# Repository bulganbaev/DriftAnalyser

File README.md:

# ZVER L8

LED-контроллер линейки ZVER, бывший DriftAnalyser (ZverCustomLed).
Репозиторий: `~/Documents/Code/ZVER/L8`; старый путь `~/Documents/Code/DriftAnalyser` удалён. GitHub: [ZverCustom/l8](https://github.com/ZverCustom/l8/tree/pcb-v3), рабочая ветка — `pcb-v3`.
Актуальная восьмиканальная плата — [PCB v3](PCB/v3/README.md). Описание прошивки и шестиканальной v2 ниже относится к предыдущей ревизии.
Общая линейка и vault: `~/Documents/Code/ZVER`, `~/Documents/Code/bobr-projects/ZVER`.

Прошивка для платы на ESP32-S3, которая управляет шестью адресными 12 В лентами (WS2815) по данным с машины. Данные берутся с CAN-шины (OBD2 или пассивно с BMW MS43), с MS43 по K-line (DS2) и со встроенного гироскопа/акселерометра LSM6DS3TR-C. Настройка через веб-интерфейс GyverHub, который отдаётся с самой платы по Wi-Fi, приложение не нужно.

## Железо

Прошивка для **платы v2** (KiCad, `PCB/v2/`, подробно в её README). Прошивка под первую
ревизию (EasyEDA, `PCB/`, MPU-6050, 5 В ленты) осталась на `main` до слияния `fw-v2`.

| Узел | Что стоит |
|---|---|
| Контроллер | ESP32-S3-WROOM-1 N16R2, USB-C на native USB |
| Ленты | 6 × JST VH, только 12 В (WS2815), данные через 74HCT245 |
| Питание лент | ключ BTS7002-1EPP, включается из прошивки, ток читается через IS |
| CAN | TJA1051, пин S (silent) управляется из прошивки |
| K-line | TJA1027, UART1, перемычка JP2 = подтяжка 510 Ом на VBAT |
| IMU | LSM6DS3TR-C, I2C 0x6A |
| SD | microSD, в прошивке пока не задействована |

### Пины (`src/pins/pins.h`)

| Сигнал | GPIO |
|---|---|
| LED 1..6 | 4, 5, 6, 7, 15, 16 |
| LED_PWR_EN (ключ лент) | 10 |
| LED_ISENSE (ADC) | 2 |
| VBAT_SENSE (ADC) | 1 |
| STATUS_LED | 11 |
| I2C SDA / SCL | 8 / 9 |
| IMU INT1 | 17 (не используется) |
| K-line RX / TX | 12 / 13 |
| CAN RX / TX / STB | 21 / 18 / 14 |
| BOOT | 0 |

### Питание лент и защита

Ключ лент выключен до первого кадра (чёрного), потом включён, пока включён Master.
Ток пересчитывается из IS: `I = V_IS × 22700 / 470`. Прошивка выключает ключ и держит
выключенным (латч), если сглаженный ток выше «LED max current» (по умолчанию 15 А)
дольше 100 мс, или если IS выше 1.6 В дольше 50 мс (сигнал fault самого BTS7002).
Сброс кнопкой «Reset power latch» на странице System. VBAT = `V × 5.7` (делитель 47k/10k).

Светодиод статуса: горит во время загрузки, мигает 1 Гц в работе, 5 Гц при сработавшем латче.

### Перемычки

- JP1 — терминатор 120 Ом на CAN. На шине машины не ставить.
- JP2 — подтяжка K-line к VBAT. Нужна, если DME сама шину не тянет; без 12 В трансивер K-line не работает вообще.

## Сборка и прошивка

PlatformIO, окружение `esp32s3box`.

```
~/.platformio/penv/bin/pio run -e esp32s3box            # сборка
~/.platformio/penv/bin/pio run -e esp32s3box -t upload  # заливка
~/.platformio/penv/bin/pio device monitor -b 115200     # монитор
```

Если `pio` есть в PATH, полный путь не нужен. В VS Code то же самое кнопками PlatformIO в статус-баре.

Плата видна как `/dev/cu.usbmodemXXXX` (native USB CDC), лог на 115200. При открытии порта плата может сброситься по DTR/RTS, это нормально.

Важное в `platformio.ini`:

| Параметр | Зачем |
|---|---|
| `board_build.partitions = default_16MB.csv` | под прошивку 6.5 МБ вместо дефолтных 1.3 МБ |
| `-D GH_INCLUDE_PORTAL` | веб-интерфейс GyverHub зашит в прошивку и отдаётся с платы |
| `-D GH_NO_STREAM` | GyverHub не льёт свои пакеты в Serial |
| `-D FASTLED_ESP32_FLASH_LOCK=1` | запись во флеш ждёт окончания вывода на ленты, иначе паника `Cache disabled but cached memory region accessed` |

Библиотека GyverHub тянется с git HEAD (репозиторий заархивирован), магазинные приложения с ней несовместимы (`Device has newer API`). Поэтому интерфейс встроен в прошивку.

### Дефолтная Wi-Fi сеть

Скопировать `src/config/secrets.example.h` в `src/config/secrets.h` и вписать SSID и пароль. Файл в `.gitignore`. Эти значения используются как стартовые при чистом файле настроек, потом меняются из интерфейса.

## Wi-Fi

Плата объявляет себя по mDNS как `zvercustom`, в той же сети интерфейс открывается по `http://zvercustom.local`.

Прошивка по Wi-Fi без кабеля, из корня проекта после `pio run`:

```
curl -F "file=@.pio/build/esp32s3box/firmware.bin" "http://zvercustom.local/hub/ota?client_id=cli&type=flash"
```

Плата сама перезагрузится, в логе на странице System будет `reboot: OTA update`. То же самое доступно кнопкой в информации об устройстве в интерфейсе.

- При старте плата подключается к сохранённой сети (STA).
- Если за 20 с не подключилась, поднимает свою точку `ZverCustomLed` / `qwerty12345`, IP 192.168.4.1, и продолжает пробовать STA каждые 30 с.
- Как только STA подключилась, точка гасится. Если STA пропала на 20 с, точка поднимается снова.
- Пустой SSID = только своя точка.
- Веб-интерфейс: `http://<ip платы>`, на точке `http://192.168.4.1` (открывается как captive portal). Только http.
- OTA-прошивка и файловый менеджер доступны во вкладке информации об устройстве в интерфейсе GyverHub.

## Веб-интерфейс

Меню сверху, шесть страниц.

### Dashboard

Главный выключатель Master, статус Wi-Fi, gauge RPM / Speed / Temp / Throttle / Lateral G / Yaw, статус CAN, кнопка Reboot.

### LEDs

Настройки выбранной ленты (Strip 1..6):

| Настройка | Что делает |
|---|---|
| Strip N enabled | вкл/выкл вывод на ленту |
| Reverse | перевернуть направление |
| Mode | Animation / Scale / Hybrid |
| Scale source | RPM / Speed / Throttle / Lateral G / Yaw rate (для Scale и Hybrid) |
| Animation | одна из 16 анимаций (для Animation, а в Hybrid — то, что крутится ниже минимума) |
| Color | цвет для одноцветных анимаций |
| Strip brightness | яркость ленты 0–100 |
| LED count | число светодиодов, 1..1000, применяется на лету |
| Color order | RGB / GRB / BGR / RBG / GBR / BRG, тоже на лету |
| Grow from middle + Middle LED | шкала растёт от указанного светодиода в обе стороны; для G и Yaw знак значения выбирает сторону |
| Apply to all strips | скопировать настройки этой ленты на остальные (кроме числа светодиодов) |

Режимы: Animation — просто анимация. Scale — шкала по выбранному источнику, семь цветовых зон от синего к пурпурному. Hybrid — шкала, когда источник выше минимума, иначе анимация.

Анимации: Static Color, Theater Chase, Color Wave, Breathing Light, Rainbow Cycle, Snake, Meteor Rain, Twinkle, Running Lights, Larson Scanner, Fire, Police, Confetti, Color Wipe, Sinelon, G Force. У каждой ленты своё состояние, две ленты на одной анимации друг другу не мешают.

Глобальные:

| Настройка | Что делает |
|---|---|
| Animation speed | частота кадров для всех анимаций (у Police и Sinelon ещё и период) |
| Global brightness | общая яркость 0–100 |
| Scale min / max RPM | диапазон шкалы по оборотам |
| Shift light RPM / Shift color | выше этого порога вся лента в режиме шкалы по RPM мигает выбранным цветом; 0 = порог равен max RPM |
| Full scale km/h / G / yaw | полная шкала для источников Speed, Lateral G, Yaw |
| Engine off / no data | что делать, когда мотор заглушен или данных нет: Keep running / Dim (до Dim to %) / Off |
| Power limit mA at 12V | программный лимит тока FastLED (оценка по яркости), 0 = выключен. Аппаратная защита — LED max current на странице System |
| Presets | три слота, Save / Load всего набора настроек лент и глобальных |

«Мотор заглушен» = нет свежих данных с CAN или обороты ниже 300.

### CAN

Выбор источника OBD2 / BMW MS43 / Sniffer (переключается на лету, драйвер перезапускается), статус драйвера и потока, сырые значения RPM / Speed / Temp / Throttle. В режиме Sniffer — таблица кадров по ID, обновляется раз в секунду.

### Wi-Fi

SSID, пароль, кнопка Reconnect, статус, IP и RSSI в сети, состояние своей точки, MAC.

### IMU

Gauge Lateral G и Yaw, выбор осей (±X / ±Y / ±Z) для поперечного ускорения и для угловой скорости, кнопка Calibrate (машина ровно, мотор заглушен — текущее показание становится нулём, смещения сохраняются), сырые значения по трём осям и температура чипа.

### System

VBAT, ток лент, состояние ключа и причина латча, «LED max current», кнопка «Reset power latch». Ниже uptime, причина последнего сброса, свободная память, дата сборки, занятость файловой системы, хвост лога, кнопки Refresh log / Clear log / Reboot.

## CAN

Скорость 500 кбит/с во всех режимах.

**OBD2.** Активный опрос mode 01 на 0x7DF, ответ ждётся с 0x7E8..0x7EF. PID 0x0C (RPM), 0x0D (скорость), 0x11 (дроссель), 0x05 (температура ОЖ), по кругу, пауза 50 мс между запросами, таймаут ответа 200 мс. Неблокирующий.

**BMW MS43.** Плата в listen-only, ничего не передаёт и не подтверждает кадры. Декодирует:

| ID | Данные | Формула |
|---|---|---|
| 0x316 (DME1) | обороты | `((b3 << 8) \| b2) / 6.4` |
| 0x329 (DME2) | температура ОЖ, дроссель | `b1 * 0.75 - 48`, `b5 * 100 / 254` |
| 0x153 (ASC1) | скорость | `((b2 << 8) \| b1) / 128` — не проверено, калибровать по дампу |

У MS43 диагностика по K-line, OBD2-запросы он не понимает. CAN между DME, приборкой, ABS и АКПП выведен на разъём X60004: пин 36 = CAN H (жёлто-красный), пин 37 = CAN L (жёлто-коричневый). Масса платы на кузов, H1 снять.

**BMW MS43 K-line (DS2).** UART1 9600 8E1, по кругу запрос статуса `12 05 0B 03 1F`, ответ
45 байт. Эхо собственного запроса трансивер возвращает, оно сверяется и отбрасывается.
Таймаут 400 мс, пауза 10 мс. CAN в этом режиме остаётся listen-only и не декодируется.

| Байт ответа | Данные | Формула |
|---|---|---|
| 3–4 | обороты | u16 big-endian |
| 5 | скорость, км/ч | как есть |
| 6–7 | педаль, ° | u16 × 0.0018311 → % по полному ходу 80° (подобрать в машине) |
| 8–9 | дроссельная заслонка, ° | u16 × 0.0018311 |
| 12 / 13 | воздух на впуске / ОЖ, °C | × 0.75 − 48 |
| 43 | напряжение, В | × 0.10156 |

Смещения из таблицы SGBD MS430DS0 (`ms430ds0_ds2.b1v`) и сверены с реальным ответом
с форума (747 об/мин, ОЖ 67.5 °C, 13.7 В), но на нашей машине **ещё не проверены**.
На странице CAN в этом режиме: декодированные значения, последний сырой кадр и поле для
произвольного запроса в hex (адрес, длина, данные; xor дописывается сам).

**Sniffer.** Listen-only, все кадры в таблицу по ID (до 64 ID): длина, последние байты, кадров в секунду, всего. Та же таблица печатается в Serial не чаще двух раз в секунду на ID.

Если данных нет 3 с, обороты, скорость и дроссель сбрасываются в 0, температура остаётся.

## Хранение настроек

Всё в LittleFS, файл `/settings.dat` через FileData. Буква-ключ в `src/settings/settings.cpp` (сейчас `'C'`) работает как версия структуры: при изменении `SavedData` или буквы файл перезаписывается дефолтами. Запись отложенная, через `fileData.update()` после изменений в интерфейсе.

Лог `/log.txt`: старт с причиной сброса и датой сборки, Wi-Fi подключился/пропал, точка поднялась, смена режима CAN, найден/потерян IMU, перезагрузки из интерфейса и по OTA. При 24 кБ переезжает в `/log.old`. Файлы можно скачать через файловый менеджер GyverHub.

## Структура исходников

| Модуль | Что делает |
|---|---|
| `src/main.cpp` | setup/loop, порядок инициализации |
| `src/config/` | AP SSID/пароль, число лент, `secrets.h` с дефолтной сетью |
| `src/pins/` | все GPIO |
| `src/settings/` | структура настроек, загрузка/сохранение, пресеты |
| `src/net/` | Wi-Fi: STA с откатом на AP, строки статуса |
| `src/hub/` | страницы GyverHub |
| `src/led_control/` | ленты: анимации, шкала, шифт-лайт, выходной буфер с реверсом/яркостью/порядком цветов, лимит тока |
| `src/can_bus/` | обёртка над TWAI, normal / listen-only, перезапуск |
| `src/obd2/` | неблокирующий опрос PID |
| `src/vehicle/` | общие данные машины, режимы CAN, декодер MS43, сниффер |
| `src/imu/` | LSM6DS3TR-C по регистрам, фильтр, калибровка, поперечное G и yaw |
| `src/power/` | ключ лент, латч по току, VBAT, светодиод статуса |
| `src/kline/` | DS2 по K-line, опрос MS43 |
| `lib/ds2/`, `lib/power_latch/` | чистая логика без Arduino, тесты `pio test -e native` |
| `src/system/` | причина сброса, uptime, лог на LittleFS |

## Известные проблемы и что дальше

- Формула скорости для 0x153 взята с форума и не проверена, сверять по сниффер-дампу на ходу.
- MS43-декодер на живой машине ещё не гонялся, начинать со Sniffer и смотреть, что летит.
- Ориентация IMU зависит от того, как плата стоит в машине: выбрать оси на странице IMU и откалибровать на ровной площадке.
- DS2-смещения и полный ход педали не проверены на машине.
- SD-карта не задействована.
- Разъёмы лент и OBD на v2 стоят вертикально, корпус под вставленные фишки надо поднимать.

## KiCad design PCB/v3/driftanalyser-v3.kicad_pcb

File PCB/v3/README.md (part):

# ZVER L8 PCB v3

Product name: ZVER L8 (formerly DriftAnalyser). Existing technical filenames and fabrication outputs retain their names.

Car LED controller: eight switched 12 V WS2812 strip channels, CAN, K-line, IMU, three inputs,
ESP32-S3. 55 × 112 mm, 6 layers, every part on the top side.

Everything is generated from `gen/` (`gen/model.py` = parts and nets, `gen/placement.py`,
`gen/pcb_builder.py` = copper, `gen/route.py` = replays the committed Freerouting session
`fab/route.ses`, `gen/export.py` = fab files). `bash gen/build.sh` rebuilds schematic, board, routing,
fab files and runs the tests. Do not hand-edit the `.kicad_sch` / `.kicad_pcb` files. What goes to
the fab and how to order it: [`fab/README-fab.md`](fab/README-fab.md).

## What is on the board

| block | parts |
| --- | --- |
| +12 V in | **J2** M6 terminal (Würth WP-BUCF REDCUBE PRESS-FIT 7461059: 13 × 13 mm brass block, internal M6 thread, 16 press-fit pins; we press it in, red boot), D1 SMCJ24CA TVS, **U2 LM74700-Q1** ideal diode with **Q1/Q2 2 × BSC016N06NS** (60 V) VIN → VBUS |
| battery negative | **J5** M6 terminal (same part, pressed in by us, black boot) = GND. The strips' return (35..40 A) comes in here and goes through In1 (solid GND) and the GND fills to J1 row 4 |
| logic supply | **U7 LMR36520** buck (VIN 4.2..65 V, abs max 70 V; replaces v2's AP63200) → 5.4 V → D6 → 5V, U8 AP7361C → 3V3; USB-C J3 (U9 ESD) feeds 5V through D8 |
| wake / hold | IGN (J1.24) or HOLD (GPIO41) enables the buck through D4/D5; IGN off and HOLD low = buck off |
| strip outputs | **U10..U13 BTS7008-2EPA** (dual high-side, exposed pad = VBUS), 8 channels × 5 A; inputs, DEN, DSEL from **U14 PCA9555 @ 0x20**; one shared IS line (R49 1.2k) to GPIO2 |
| strip data | U15/U16 74HCT245 (3V3 → 5 V), 33 R series + PESD5V0S1BA per line |
| comms | U4 TJA1051T/3 CAN (JP2 120 R termination), U5 TJA1027 K-line (JP1 510 R pull-up to VBUS), D20 PESD1CAN |
| inputs | IN1..IN3: SMAJ24A, 10k / 33k / 10k divider to the ADC, switchable 10k pull (see firmware notes) |
| sensor 5 V | U6 TPS2553 (~130 mA limit, EN / FAULT on U14 / GPIO47), D7 reverse block, out on J1.23 |
| MCU | U1 ESP32-S3-WROOM-1U-N16R2 (u.FL), U3 LSM6DS3TR-C IMU (I2C 0x6A), SW1 BOOT, SW2 EN, J4 UART0 |

## J1 pinout (TE 6437288-1, Superseal 1.0, 34 pos)

Re-pinned during routing (task 11 ruling, spec §3 note): all eight LEDn +12 V in row 1, each right
above its own switch output; the eight strip grounds in row 4, each in the same column as its +12 V;
data, CAN, K-line, IGN, inputs and the sensor 5 V in rows 2–3. Pin numbers are TE's, as moulded on
the housing.

<!-- j1-table: generated by gen/export.py, do not edit -->

| row | pin | net | signal |
| --- | --- | --- | --- |
| 1 | 1 | `LED2_12V` | LED2 +12 V (U10 OUT1) |
| 1 | 2 | `LED1_12V` | LED1 +12 V (U10 OUT0) |
| 1 | 3 | `LED6_12V` | LED6 +12 V (U12 OUT1) |
| 1 | 4 | `LED5_12V` | LED5 +12 V (U12 OUT0) |
| 1 | 5 | `GND` | GND, signal return |
| 1 | 6 | `LED4_12V` | LED4 +12 V (U11 OUT1) |
| 1 | 7 | `LED3_12V` | LED3 +12 V (U11 OUT0) |
| 1 | 8 | `LED8_12V` | LED8 +12 V (U13 OUT1) |
| 1 | 9 | `LED7_12V` | LED7 +12 V (U13 OUT0) |
| 2 | 10 | `LED2_DO` | LED2 data |
| 2 | 11 | `LED1_DO` | LED1 data |
| 2 | 12 | `LED6_DO` | LED6 data |
| 2 | 13 | `LED5_DO` | LED5 data |
| 2 | 14 | `IN1` | input 1 |
| 2 | 15 | `LED4_DO` | LED4 data |
| 2 | 16 | `LED3_DO` | LED3 data |
| 2 | 17 | `LED8_DO` | LED8 data |
| 3 | 18 | `CANH` | CAN high |
| 3 | 19 | `CANL` | CAN low |
| 3 | 20 | `KLINE` | K-line |
| 3 | 21 | `IN2` | input 2 |
| 3 | 22 | `IN3` | input 3 |
| 3 | 23 | `5V_SENS` | 5 V sensor supply (U6, switched, ~130 mA limit) |
| 3 | 24 | `IGN` | ignition (wakes the board) |
| 3 | 25 | `LED7_DO` | LED7 data |
| 4 | 26 | `GND` | GND, LED2 strip return |
| 4 | 27 | `GND` | GND, LED1 strip return |
| 4 | 28 | `GND` | GND, LED6 strip return |
| 4 | 29 | `GND` | GND, LED5 strip return |
| 4 | 30 | `GND` | GND, signal return |
| 4 | 31 | `GND` | GND, LED4 strip return |
| 4 | 32 | `GND` | GND, LED3 strip return |
| 4 | 33 | `GND` | GND, LED8 strip return |
| 4 | 34 | `GND` | GND, LED7 strip return |

Top view, J1 at the top edge (mating face toward the edge, row 4 nearest it):

```
row 4: 34 LED7_GND     33 LED8_GND     32 LED3_GND     31 LED4_GND     30 SIG2_GND     29 LED5_GND     28 LED6_GND     27 LED1_GND     26 LED2_GND
row 3:         25 LED7_DO      24 IGN          23 5V_SENS      22 IN3          21 IN2          20 KLINE        19 CANL         18 CANH
row 2:         17 LED8_DO      16 LED3_DO      15 LED4_DO      14 IN1          13 LED5_DO      12 LED6_DO      11 LED1_DO      10 LED2_DO
row 1:  9 LED7_12V      8 LED8_12V      7 LED3_12V      6 LED4_12V      5 SIG1_GND      4 LED5_12V      3 LED6_12V      2 LED1_12V      1 LED2_12V
```

<!-- /j1-table -->

Harness: crimp by pin number, not by position or wire colour. Each strip is three wires on three
fixed pins: its +12 V in row 1, its ground in row 4 straight below that, its data in row 2 or 3 (see
the table). Keep each strip's +12 V and ground in the same cable. CANH/CANL (18/19) are a twisted
pair. Pins 5 and 30 are signal grounds for the sensor / input side. Every cavity is used, so no
sealing plugs are needed.

## Jumpers

| jumper | fitted | open |
| --- | --- | --- |
| JP1 (silk "JP1 K-LINE") | 510 R K-line pull-up to VBUS: car without its own pull-up / board is the master | CAN-only car, or the bus already has a pull-up |
| JP2 (silk "JP2 CAN TERM") | 120 R between CANH and CANL: board is an end of the bus | board is a stub on a terminated bus (the usual OBD case) |

## Quiescent current

Target ≤ 1 mA from the studs with IGN off (spec). With IGN off and HOLD low the buck is shut down
(R7 holds EN at 0 V, 5.3 µA typ) and everything on 5V / 3V3 is unpowered. What stays on VBUS / VIN,
from the datasheets (estimate, **not measured**):

| what | current |
| --- | --- |
| R1/R2 battery sense divider (470k + 100k) | ~22 µA at 12.6 V (≤ 30 µA even if D2 back-feeds the unpowered 3V3) |
| U2 LM74700 (EN tied to the anode, always on) | ~80 µA typ |
| U7 LMR36520 in shutdown | ~5 µA |
| U10..U13 BTS7008 standby, U5 TJA1027 VBAT, TVS leakage | a few µA each |
| total | ~0.1..0.2 mA |

## Firmware notes (fw-v3)

- **Updates over the air only.** The case has no USB opening: J3 USB-C is for the first flash and
  recovery with the lid off. fw-v3 must keep OTA safe: two app slots (`ota_0`/`ota_1` in a 16 MB
  partition table), rollback if the new image does not confirm itself, and OTA reachable from the
  web UI over the unit's own Wi-Fi AP.
- Pin map: `gen/pinmap.py` (ESP32 GPIOs and the PCA9555 ports). U14 PCA9555 is at **I2C 0x20**:
  P00..P07 = LED1..8 IN, P10..P13 = DEN1..4, P14 = DSEL, P15 = CAN_S, P16 = status LED, P17 = sensor 5 V EN.
  Every switch input has a 10k pull-down, so all channels are off until the expander is written.
- BTS7008: switch k (U(9+k)) drives LED(2k−1) on OUT0 and LED(2k) on OUT1. Current sense: raise one
  DENk, then **DSEL = 0 → IS = OUT0 = LED(2k−1), DSEL = 1 → IS = OUT1 = LED(2k)**. The four IS pins
  share LED_ISENSE (GPIO2): kILIS 5450 into 1.2k → ~0.22 V per A (5 A ≈ 1.1 V); a fault reads full
  scale (clamped). Only one DEN high at a time.
- Power: IGN wakes the buck. Firmware sets **HOLD (GPIO41) high** to stay on after IGN drops, and
  low to power off. **Keep HOLD low on USB-only power** (VBAT_SENSE ≈ 0): the buck's EN must not sit
  above VIN + 0.3 V. IGN_DET (GPIO40) is a digital IGN-present input. VBAT_SENSE (GPIO1) = VBUS × 100/570 (470k / 100k, 82k source: sample
  slowly, C5 100 nF holds it).
- CAN: **CAN_S (P15) high = silent** (listen-only), and R70 pulls it high, so the board never drives
  the bus until firmware sets CAN_S low.
- Inputs IN1..3: the 10k pull on `INn_PULL` acts on the ADC node (`INn_SENSE`), behind the 10k / 33k
  divider. With the pull-up on (GPIO high), an open input reads **≈ 1.65 V** and an input shorted to
  GND **≈ 1.48 V**; with the pull-down on (GPIO low), 12 V on the input reads **≈ 1.25 V**. GPIO as
  input = no pull.
- 5V_SENS: enable with P17, overcurrent = SENS_5V_FLT (GPIO47) low.
- **Strip data while a channel is off:** drive LEDn_DATA low (GPIO low, or idle the RMT channel low)
  whenever that channel's switch is off. U15/U16 (74HCT245) run from 5 V and keep driving their
  outputs: a high DATA line into an unpowered strip back-powers its first LED through the data pin.

## Bring-up checklist (first board)

1. **Before fab, still open:**
   - **J1 (TE 6437288-1) geometry checked 2026-10-18** against TE customer drawing
     C-9-1437287-8 rev A1, sheet 2 (34 pos): mounting holes Ø3.3 at 38.5, nearest pin row 6.5 from
     them, rows 2.5 / 3 / 2.5 apart, 3 mm pitch, 8-pin rows offset 1.5, outer 9-pin row starts 7.25
     from the mounting hole, through holes Ø1.3 +0.2 (ours drill 1.4) — all match
     `da3:TE_6437288-1`. **Still must-check before crimping a harness: pin numbering.** That drawing
     gives no cavity numbers; our footprint puts 1–9 in the row farthest from the mounting holes
     (top row of the mating face), pin 1 at the left seen from the component side. Confirm with the
     mating plug 4-1437290-0 drawing or the moulded numbers on the housing.
   - LMR36520 exposed-pad mask: KiCad's footprint opens 2.4 × 3.1 mm, TI's DDA0008B example
     2.71 × 3.4 mm. Decide whether to enlarge it.
   - Thermal pad in the case must be electrically insulating: the B.Cu under U10..U13 is VBUS.
   - Order with **ENIG** and the press-fit hole note (`fab/README-fab.md`): 32 holes at J2/J5,
     finished **1.475 ± 0.05 mm**.
   - Done in the final review: J2/J5 footprint `da3:Wurth_REDCUBE_7461059` drawn from Würth drawing
     7461059 rev 001.003 (2025-02-04); Q1/Q2 land `da3:Infineon_TDSON-8_FL` checked against
     the BSC016N06NS datasheet rev 2.6 Fig 2 (KiCad's `TDSON-8-1` lead pads were 0.85 long with a
     1.25 gap; now 1.10 long with Infineon's 1.00 gap, gate 0.90 - see the footprint's descr).
2. **Press the studs in** (J2, J5, Würth 7461059) after JLC's assembly: arbor press, one straight
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
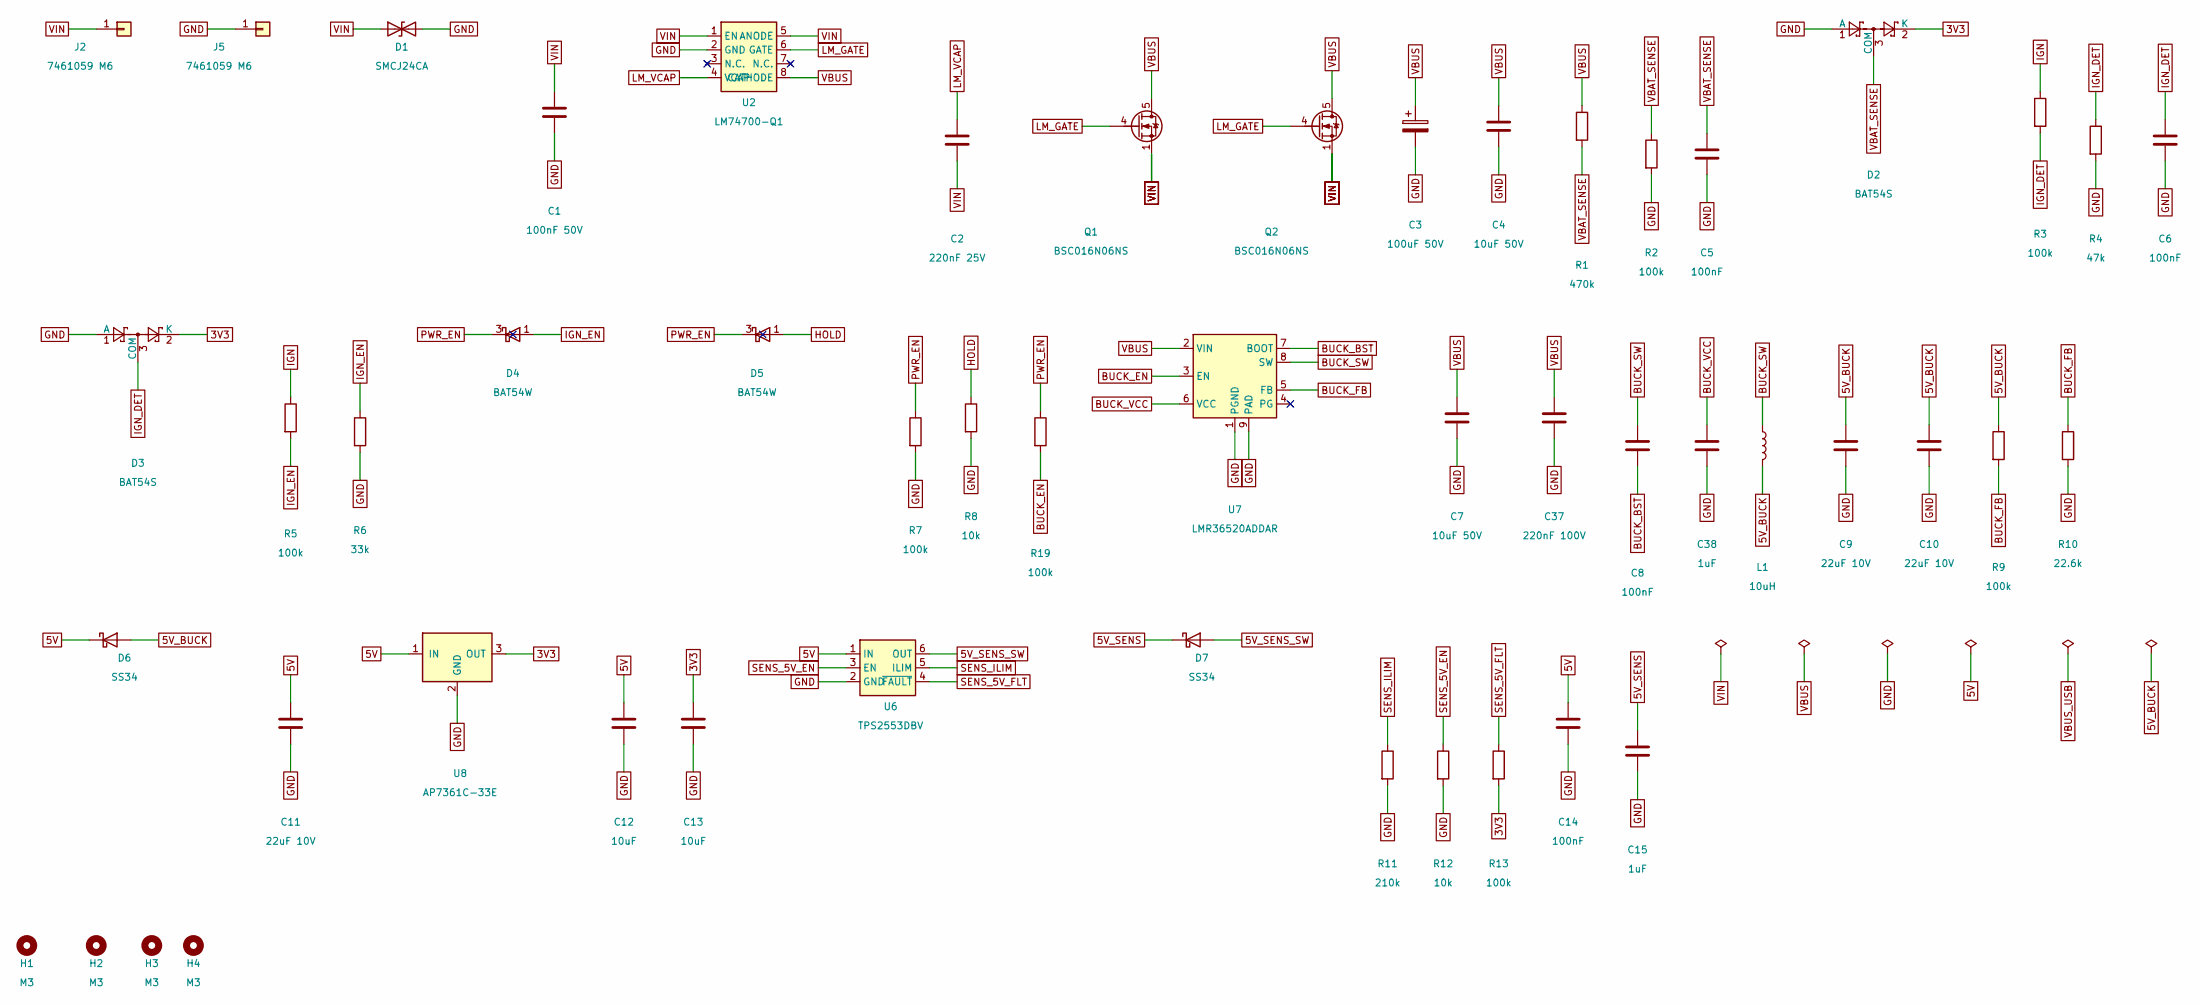
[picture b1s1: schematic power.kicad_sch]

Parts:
C1: 100nF 50V; C_0603_1608Metric; MPN CC0603KRX7R9BB104; LCSC C14663
C2: 220nF 25V; C_0603_1608Metric; MPN CL10B224KA8NNNC; LCSC C21120
C3: 100uF 50V; CP_Elec_8x10.5; MPN GVZ1H107M0810CNVC; LCSC C2983550
C4, C7: 10uF 50V; C_1210_3225Metric; MPN CS3225X7R106K500NRL; LCSC C2918502
C5, C6, C8, C14: 100nF; C_0603_1608Metric; MPN CC0603KRX7R9BB104; LCSC C14663
C9, C10, C11: 22uF 10V; C_0805_2012Metric; MPN CL21A226MAQNNNE; LCSC C45783
C12, C13: 10uF; C_0805_2012Metric; MPN CL21A106KAYNNNE; LCSC C15850
C15, C38: 1uF; C_0603_1608Metric; MPN CL10A105KB8NNNC; LCSC C15849
C37: 220nF 100V; C_0805_2012Metric; MPN CC0805KKX7R0BB224; LCSC C513710
D1: SMCJ24CA; D_SMC; MPN SMCJ24CA; LCSC C151279
D2, D3: BAT54S; SOT-23; MPN BAT54S,215; LCSC C47546
D4, D5: BAT54W; SOT-323_SC-70; MPN BAT54W; LCSC C77328
D6, D7: SS34; D_SMA; MPN SS34; LCSC C8678
H1, H2, H3, H4: M3; MountingHole_3.2mm_M3
J2, J5: 7461059 M6; Wurth_REDCUBE_7461059; MPN 7461059 (hand-fit)
L1: 10uH; L_Bourns_SRN6045TA; MPN SRN6045TA-100M; LCSC C2046332
Q1, Q2: BSC016N06NS; Infineon_TDSON-8_FL; MPN BSC016N06NS; LCSC C454269
R1: 470k; R_0603_1608Metric; MPN 0603WAF4703T5E; LCSC C23178
R2, R3, R5, R7, R9, R13, R19: 100k; R_0603_1608Metric; MPN 0603WAF1003T5E; LCSC C25803
R4: 47k; R_0603_1608Metric; MPN 0603WAF4702T5E; LCSC C25819
R6: 33k; R_0603_1608Metric; MPN 0603WAF3302T5E; LCSC C4216
R8, R12: 10k; R_0603_1608Metric; MPN 0603WAF1002T5E; LCSC C25804
R10: 22.6k; R_0603_1608Metric; MPN CR0603FA2262G; LCSC C100874
R11: 210k; R_0603_1608Metric; MPN 0603WAF2103T5E; LCSC C22952
U2: LM74700-Q1; SOT-23-8; MPN LM74700QDDFRQ1; LCSC C3236229
U6: TPS2553DBV; SOT-23-6; MPN TPS2553DBVR; LCSC C55266
U7: LMR36520ADDAR; Texas_HTSOP-8-1EP_3.9x4.9mm_P1.27mm_EP2.95x4.9mm_Mask2.4x3.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; MPN LMR36520ADDAR; LCSC C2879422
U8: AP7361C-33E; SOT-223-3_TabPin2; MPN AP7361C-33E-13; LCSC C500795

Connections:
3V3: C13.1, D2.2 (K), D3.2 (K), R13.2, U8.3 (OUT); also elsewhere on the board
5V: C11.1, C12.1, C14.1, D6.1 (K), U6.1 (IN), U8.1 (IN); also elsewhere on the board
5V_BUCK: C9.1, C10.1, D6.2 (A), L1.2, R9.1
5V_SENS: C15.1, D7.1 (K); also elsewhere on the board
5V_SENS_SW: D7.2 (A), U6.6 (OUT)
BUCK_BST: C8.2, U7.7 (BOOT)
BUCK_EN: R19.2, U7.3 (EN)
BUCK_FB: R9.2, R10.1, U7.5 (FB)
BUCK_SW: C8.1, L1.1, U7.8 (SW)
BUCK_VCC: C38.1, U7.6 (VCC)
GND: C1.2, C3.2, C4.2, C5.2, C6.2, C7.2, C9.2, C10.2, C11.2, C12.2, C13.2, C14.2, C15.2, C37.2, C38.2, D1.2 (A2), D2.1 (A), D3.1 (A), J5.1, R2.2, R4.2, R6.2, R7.2, R8.2, R10.2, R11.2, R12.2, U2.2 (GND), U6.2 (GND), U7.1 (PGND), U7.9 (PAD), U8.2 (GND); also elsewhere on the board
HOLD: D5.1 (A), R8.1; also elsewhere on the board
IGN: R3.1, R5.1; also elsewhere on the board
IGN_DET: C6.1, D3.3 (COM), R3.2, R4.1; also elsewhere on the board
IGN_EN: D4.1 (A), R5.2, R6.1
LM_GATE: Q1.4 (G), Q2.4 (G), U2.6 (GATE)
LM_VCAP: C2.1, U2.4 (VCAP)
PWR_EN: D4.3 (K), D5.3 (K), R7.1, R19.1
SENS_5V_EN: R12.1, U6.3 (EN); also elsewhere on the board
SENS_5V_FLT: R13.1, U6.4 (~FAULT); also elsewhere on the board
SENS_ILIM: R11.1, U6.5 (ILIM)
VBAT_SENSE: C5.1, D2.3 (COM), R1.2, R2.1; also elsewhere on the board
VBUS: C3.1, C4.1, C7.1, C37.1, Q1.5 (D), Q2.5 (D), R1.1, U2.8 (CATHODE), U7.2 (VIN); also elsewhere on the board
VIN: C1.1, C2.2, D1.1 (A1), J2.1, Q1.1 (S), Q1.2 (S), Q1.3 (S), Q2.1 (S), Q2.2 (S), Q2.3 (S), U2.1 (EN), U2.5 (ANODE)

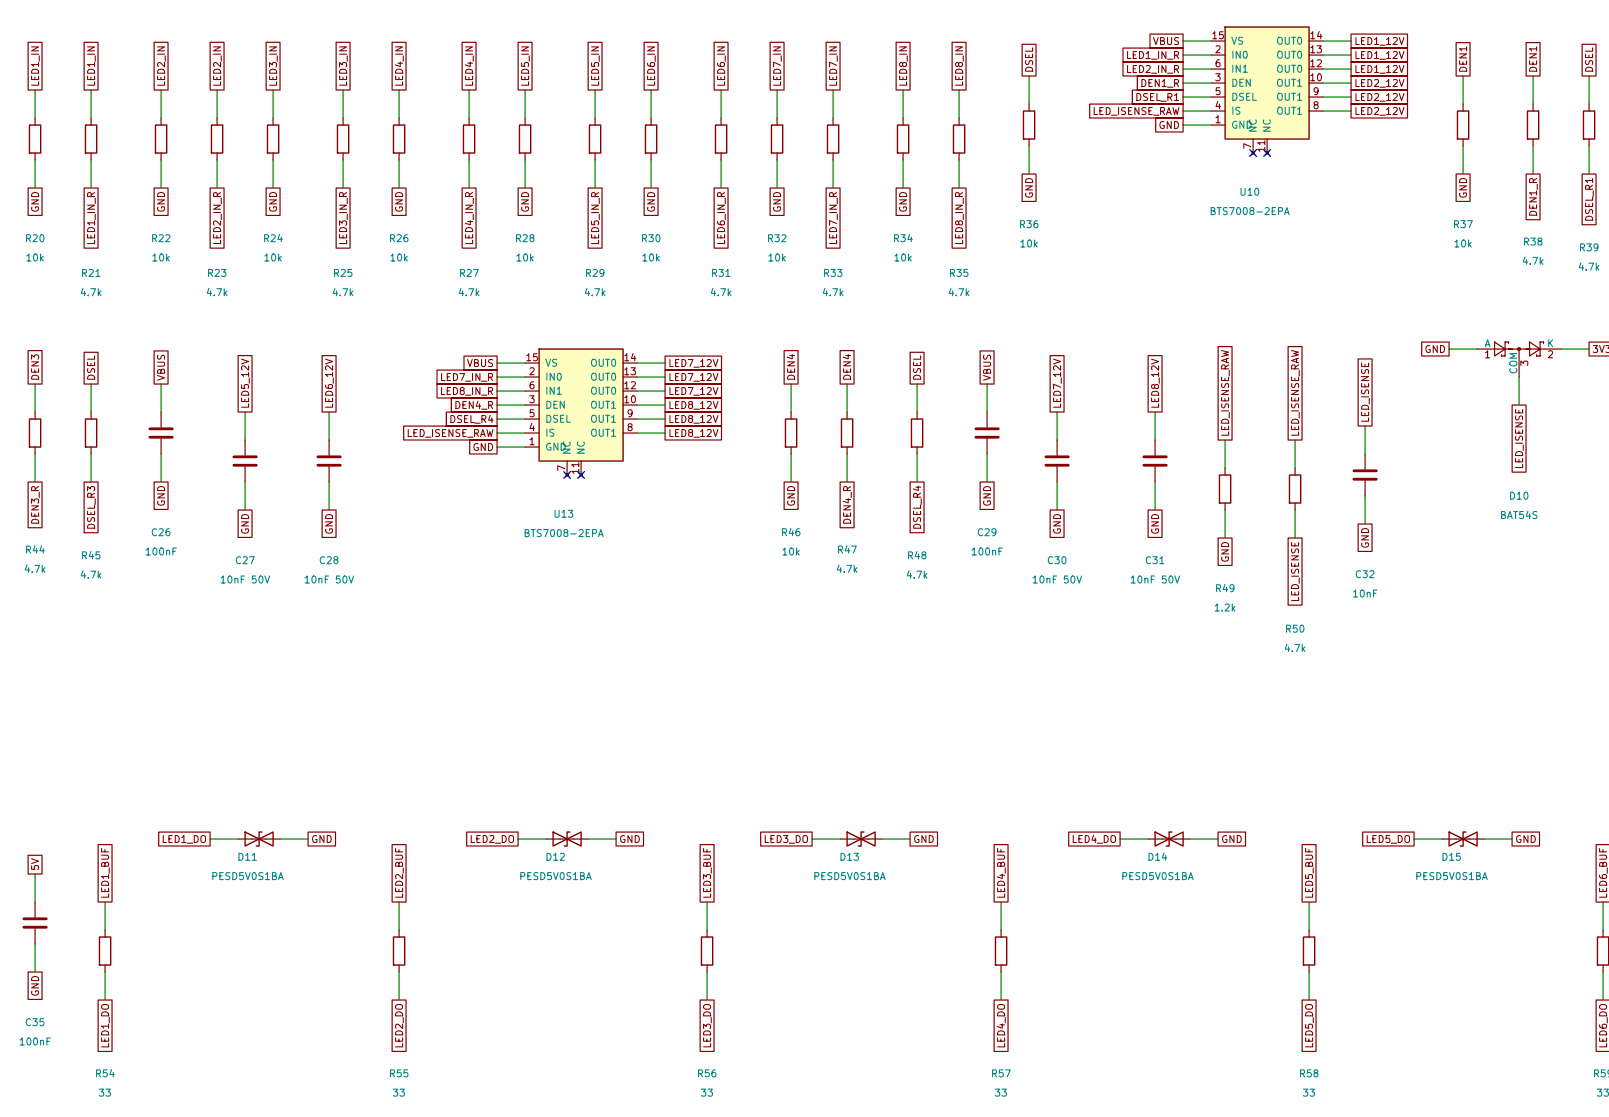
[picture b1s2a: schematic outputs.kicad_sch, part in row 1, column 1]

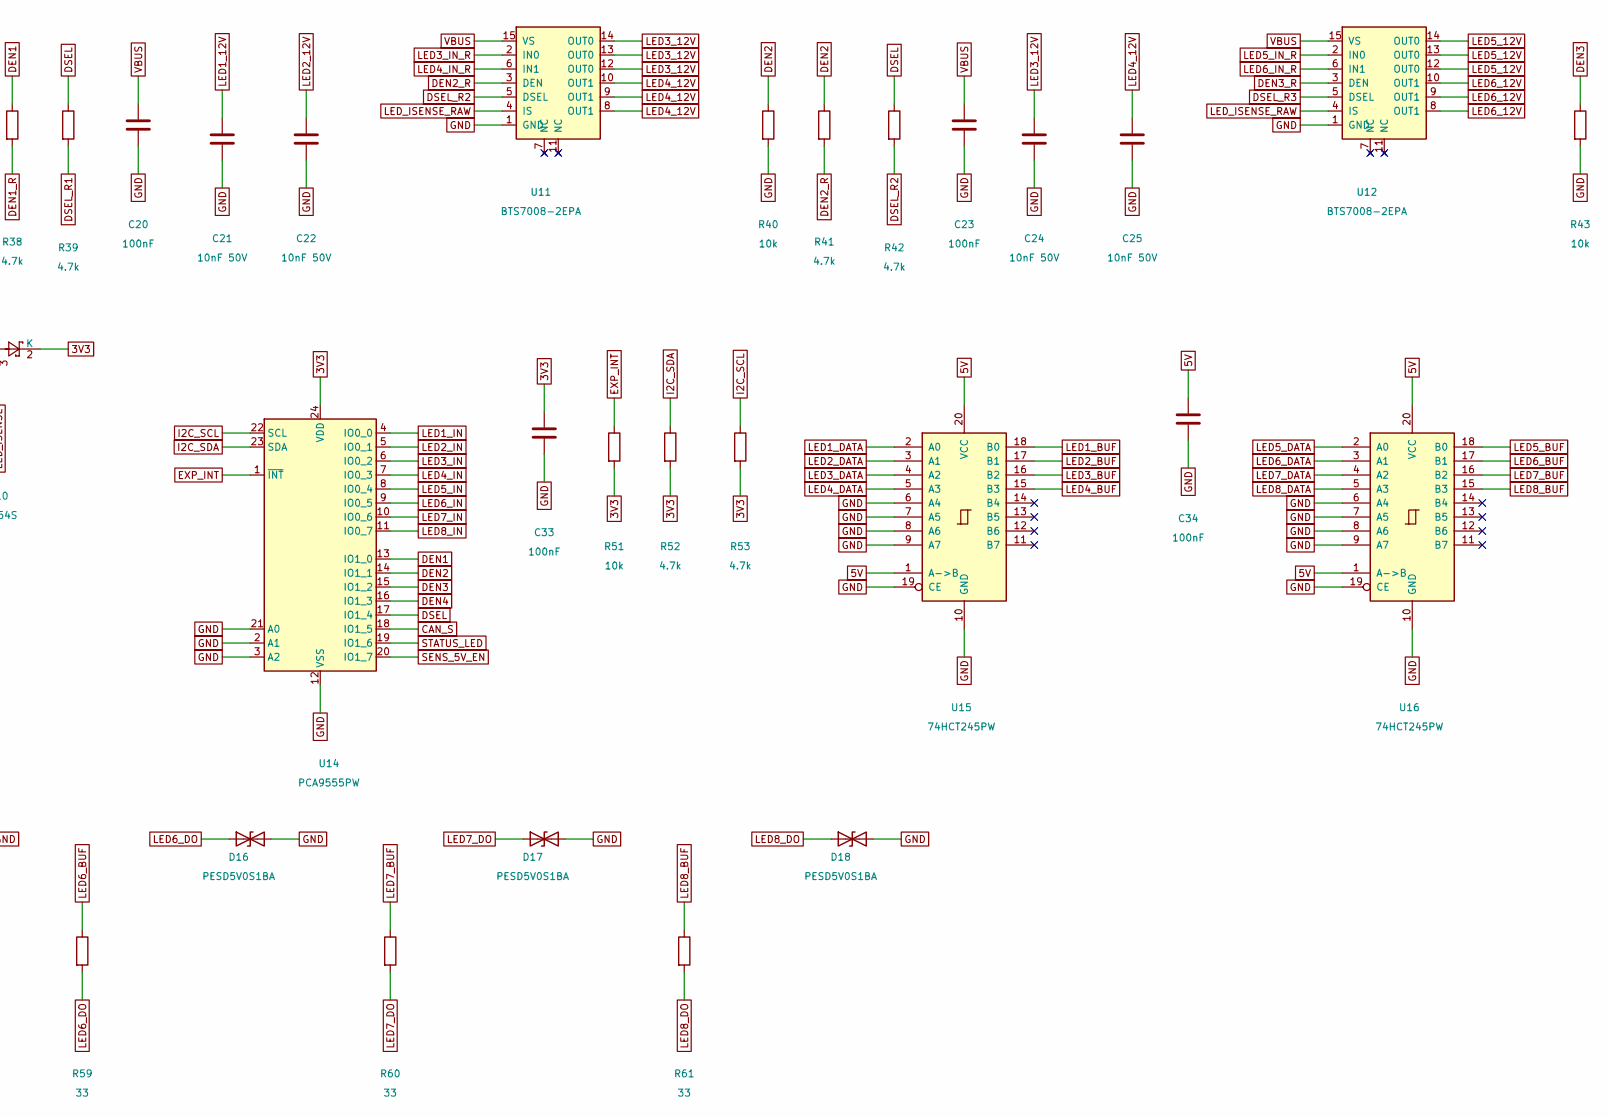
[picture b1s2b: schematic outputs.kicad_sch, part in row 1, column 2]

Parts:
C20, C23, C26, C29, C33, C34, C35: 100nF; C_0603_1608Metric; MPN CC0603KRX7R9BB104; LCSC C14663
C21, C22, C24, C25, C27, C28, C30, C31: 10nF 50V; C_0603_1608Metric; MPN 0603B103K500NT; LCSC C57112
C32: 10nF; C_0603_1608Metric; MPN 0603B103K500NT; LCSC C57112
D10: BAT54S; SOT-23; MPN BAT54S,215; LCSC C47546
D11, D12, D13, D14, D15, D16, D17, D18: PESD5V0S1BA; D_SOD-323; MPN PESD5V0S1BA,115; LCSC C19224
R20, R22, R24, R26, R28, R30, R32, R34, R36, R37, R40, R43, R46, R51: 10k; R_0603_1608Metric; MPN 0603WAF1002T5E; LCSC C25804
R21, R23, R25, R27, R29, R31, R33, R35, R38, R39, R41, R42, R44, R45, R47, R48, R50, R52, R53: 4.7k; R_0603_1608Metric; MPN 0603WAF4701T5E; LCSC C23162
R49: 1.2k; R_0603_1608Metric; MPN 0603WAF1201T5E; LCSC C22765
R54, R55, R56, R57, R58, R59, R60, R61: 33; R_0603_1608Metric; MPN 0603WAF330JT5E; LCSC C23140
U10, U11, U12, U13: BTS7008-2EPA; PG-TSDSO-14; MPN BTS7008-2EPA; LCSC C534830
U14: PCA9555PW; TSSOP-24_4.4x7.8mm_P0.65mm; MPN PCA9555PW,118; LCSC C128392
U15, U16: 74HCT245PW; TSSOP-20_4.4x6.5mm_P0.65mm; MPN 74HCT245PW,118; LCSC C5980

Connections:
3V3: C33.1, D10.2 (K), R51.2, R52.2, R53.2, U14.24 (VDD); also elsewhere on the board
5V: C34.1, C35.1, U15.1 (A->B), U15.20 (VCC), U16.1 (A->B), U16.20 (VCC); also elsewhere on the board
CAN_S: U14.18 (IO1_5); also elsewhere on the board
DEN1: R37.1, R38.1, U14.13 (IO1_0)
DEN1_R: R38.2, U10.3 (DEN)
DEN2: R40.1, R41.1, U14.14 (IO1_1)
DEN2_R: R41.2, U11.3 (DEN)
DEN3: R43.1, R44.1, U14.15 (IO1_2)
DEN3_R: R44.2, U12.3 (DEN)
DEN4: R46.1, R47.1, U14.16 (IO1_3)
DEN4_R: R47.2, U13.3 (DEN)
DSEL: R36.1, R39.1, R42.1, R45.1, R48.1, U14.17 (IO1_4)
DSEL_R1: R39.2, U10.5 (DSEL)
DSEL_R2: R42.2, U11.5 (DSEL)
DSEL_R3: R45.2, U12.5 (DSEL)
DSEL_R4: R48.2, U13.5 (DSEL)
EXP_INT: R51.1, U14.1 (~INT); also elsewhere on the board
GND: C20.2, C21.2, C22.2, C23.2, C24.2, C25.2, C26.2, C27.2, C28.2, C29.2, C30.2, C31.2, C32.2, C33.2, C34.2, C35.2, D10.1 (A), D11.2 (A2), D12.2 (A2), D13.2 (A2), D14.2 (A2), D15.2 (A2), D16.2 (A2), D17.2 (A2), D18.2 (A2), R20.2, R22.2, R24.2, R26.2, R28.2, R30.2, R32.2, R34.2, R36.2, R37.2, R40.2, R43.2, R46.2, R49.2, U10.1 (GND), U11.1 (GND), U12.1 (GND), U13.1 (GND), U14.2 (A1), U14.3 (A2), U14.12 (VSS), U14.21 (A0), U15.6 (A4), U15.7 (A5), U15.8 (A6), U15.9 (A7), U15.10 (GND), U15.19 (CE), U16.6 (A4), U16.7 (A5), U16.8 (A6), U16.9 (A7), U16.10 (GND), U16.19 (CE); also elsewhere on the board
I2C_SCL: R53.1, U14.22 (SCL); also elsewhere on the board
I2C_SDA: R52.1, U14.23 (SDA); also elsewhere on the board
LED1_12V: C21.1, U10.12 (OUT0), U10.13 (OUT0), U10.14 (OUT0); also elsewhere on the board
LED1_BUF: R54.1, U15.18 (B0)
LED1_DATA: U15.2 (A0); also elsewhere on the board
LED1_DO: D11.1 (A1), R54.2; also elsewhere on the board
LED1_IN: R20.1, R21.1, U14.4 (IO0_0)
LED1_IN_R: R21.2, U10.2 (IN0)
LED2_12V: C22.1, U10.8 (OUT1), U10.9 (OUT1), U10.10 (OUT1); also elsewhere on the board
LED2_BUF: R55.1, U15.17 (B1)
LED2_DATA: U15.3 (A1); also elsewhere on the board
LED2_DO: D12.1 (A1), R55.2; also elsewhere on the board
LED2_IN: R22.1, R23.1, U14.5 (IO0_1)
LED2_IN_R: R23.2, U10.6 (IN1)
LED3_12V: C24.1, U11.12 (OUT0), U11.13 (OUT0), U11.14 (OUT0); also elsewhere on the board
LED3_BUF: R56.1, U15.16 (B2)
LED3_DATA: U15.4 (A2); also elsewhere on the board
LED3_DO: D13.1 (A1), R56.2; also elsewhere on the board
LED3_IN: R24.1, R25.1, U14.6 (IO0_2)
LED3_IN_R: R25.2, U11.2 (IN0)
LED4_12V: C25.1, U11.8 (OUT1), U11.9 (OUT1), U11.10 (OUT1); also elsewhere on the board
LED4_BUF: R57.1, U15.15 (B3)
LED4_DATA: U15.5 (A3); also elsewhere on the board
LED4_DO: D14.1 (A1), R57.2; also elsewhere on the board
LED4_IN: R26.1, R27.1, U14.7 (IO0_3)
LED4_IN_R: R27.2, U11.6 (IN1)
LED5_12V: C27.1, U12.12 (OUT0), U12.13 (OUT0), U12.14 (OUT0); also elsewhere on the board
LED5_BUF: R58.1, U16.18 (B0)
LED5_DATA: U16.2 (A0); also elsewhere on the board
LED5_DO: D15.1 (A1), R58.2; also elsewhere on the board
LED5_IN: R28.1, R29.1, U14.8 (IO0_4)
LED5_IN_R: R29.2, U12.2 (IN0)
LED6_12V: C28.1, U12.8 (OUT1), U12.9 (OUT1), U12.10 (OUT1); also elsewhere on the board
LED6_BUF: R59.1, U16.17 (B1)
LED6_DATA: U16.3 (A1); also elsewhere on the board
LED6_DO: D16.1 (A1), R59.2; also elsewhere on the board
LED6_IN: R30.1, R31.1, U14.9 (IO0_5)
LED6_IN_R: R31.2, U12.6 (IN1)
LED7_12V: C30.1, U13.12 (OUT0), U13.13 (OUT0), U13.14 (OUT0); also elsewhere on the board
LED7_BUF: R60.1, U16.16 (B2)
LED7_DATA: U16.4 (A2); also elsewhere on the board
LED7_DO: D17.1 (A1), R60.2; also elsewhere on the board
LED7_IN: R32.1, R33.1, U14.10 (IO0_6)
LED7_IN_R: R33.2, U13.2 (IN0)
LED8_12V: C31.1, U13.8 (OUT1), U13.9 (OUT1), U13.10 (OUT1); also elsewhere on the board
LED8_BUF: R61.1, U16.15 (B3)
LED8_DATA: U16.5 (A3); also elsewhere on the board
LED8_DO: D18.1 (A1), R61.2; also elsewhere on the board
LED8_IN: R34.1, R35.1, U14.11 (IO0_7)
LED8_IN_R: R35.2, U13.6 (IN1)
LED_ISENSE: C32.1, D10.3 (COM), R50.2; also elsewhere on the board
LED_ISENSE_RAW: R49.1, R50.1, U10.4 (IS), U11.4 (IS), U12.4 (IS), U13.4 (IS)
SENS_5V_EN: U14.20 (IO1_7); also elsewhere on the board
STATUS_LED: U14.19 (IO1_6); also elsewhere on the board
VBUS: C20.1, C23.1, C26.1, C29.1, U10.15 (VS), U11.15 (VS), U12.15 (VS), U13.15 (VS); also elsewhere on the board

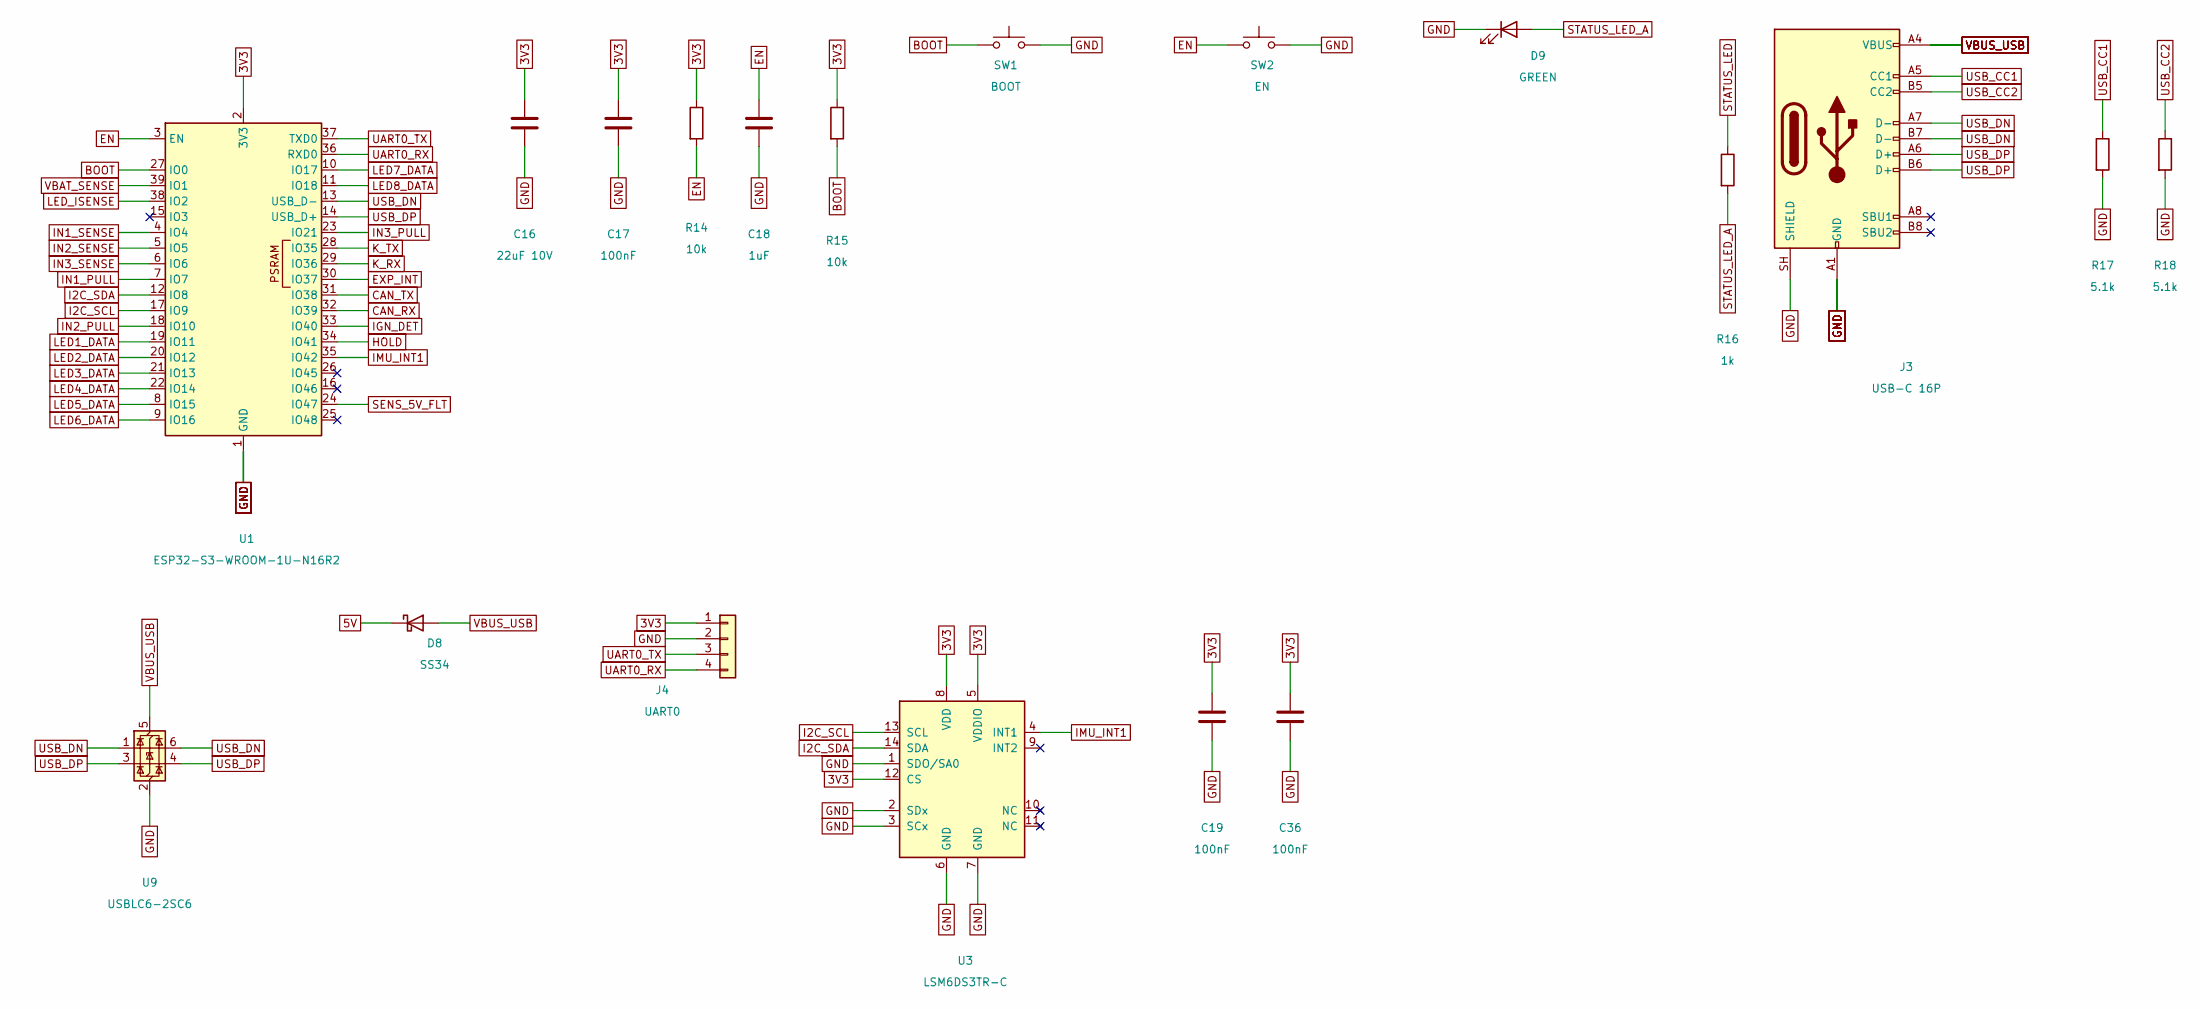
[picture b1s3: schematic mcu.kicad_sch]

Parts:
C16: 22uF 10V; C_0805_2012Metric; MPN CL21A226MAQNNNE; LCSC C45783
C17, C19, C36: 100nF; C_0603_1608Metric; MPN CC0603KRX7R9BB104; LCSC C14663
C18: 1uF; C_0603_1608Metric; MPN CL10A105KB8NNNC; LCSC C15849
D8: SS34; D_SMA; MPN SS34; LCSC C8678
D9: GREEN; LED_0603_1608Metric; MPN PSC-1608U49GC-G4; LCSC C22371299
J3: USB-C 16P; USB_C_Receptacle_HRO_TYPE-C-31-M-12; MPN TYPE-C 16PIN 2MD(073); LCSC C2765186
J4: UART0; PinHeader_1x04_P2.54mm_Vertical; MPN PZ254V-11-04P; LCSC C2691448
R14, R15: 10k; R_0603_1608Metric; MPN 0603WAF1002T5E; LCSC C25804
R16: 1k; R_0603_1608Metric; MPN 0603WAF1001T5E; LCSC C21190
R17, R18: 5.1k; R_0603_1608Metric; MPN 0603WAF5101T5E; LCSC C23186
SW1: BOOT; SW_SPST_PTS645Sx43SMTR92; MPN PTS645SM43SMTR92LFS; LCSC C221880
SW2: EN; SW_SPST_PTS645Sx43SMTR92; MPN PTS645SM43SMTR92LFS; LCSC C221880
U1: ESP32-S3-WROOM-1U-N16R2; ESP32-S3-WROOM-1U; MPN ESP32-S3-WROOM-1U-N16R2; LCSC C3013945
U3: LSM6DS3TR-C; LGA-14_3x2.5mm_P0.5mm_LayoutBorder3x4y; MPN LSM6DS3TR-C; LCSC C967633
U9: USBLC6-2SC6; SOT-23-6; MPN USBLC6-2SC6; LCSC C7519

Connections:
3V3: C16.1, C17.1, C19.1, C36.1, J4.1, R14.1, R15.1, U1.2 (3V3), U3.5 (VDDIO), U3.8 (VDD), U3.12 (CS); also elsewhere on the board
5V: D8.1 (K); also elsewhere on the board
BOOT: R15.2, SW1.1, U1.27 (IO0)
CAN_RX: U1.32 (IO39); also elsewhere on the board
CAN_TX: U1.31 (IO38); also elsewhere on the board
EN: C18.1, R14.2, SW2.1, U1.3 (EN)
EXP_INT: U1.30 (IO37); also elsewhere on the board
GND: C16.2, C17.2, C18.2, C19.2, C36.2, D9.1 (K), J3.A1 (GND), J3.A12 (GND), J3.B1 (GND), J3.B12 (GND), J3.SH (SHIELD), J4.2, R17.2, R18.2, SW1.2, SW2.2, U1.1 (GND), U1.40 (GND), U1.41 (GND), U3.1 (SDO/SA0), U3.2 (SDx), U3.3 (SCx), U3.6 (GND), U3.7 (GND), U9.2 (GND); also elsewhere on the board
HOLD: U1.34 (IO41); also elsewhere on the board
I2C_SCL: U1.17 (IO9), U3.13 (SCL); also elsewhere on the board
I2C_SDA: U1.12 (IO8), U3.14 (SDA); also elsewhere on the board
IGN_DET: U1.33 (IO40); also elsewhere on the board
IMU_INT1: U1.35 (IO42), U3.4 (INT1)
IN1_PULL: U1.7 (IO7); also elsewhere on the board
IN1_SENSE: U1.4 (IO4); also elsewhere on the board
IN2_PULL: U1.18 (IO10); also elsewhere on the board
IN2_SENSE: U1.5 (IO5); also elsewhere on the board
IN3_PULL: U1.23 (IO21); also elsewhere on the board
IN3_SENSE: U1.6 (IO6); also elsewhere on the board
K_RX: U1.29 (IO36); also elsewhere on the board
K_TX: U1.28 (IO35); also elsewhere on the board
LED1_DATA: U1.19 (IO11); also elsewhere on the board
LED2_DATA: U1.20 (IO12); also elsewhere on the board
LED3_DATA: U1.21 (IO13); also elsewhere on the board
LED4_DATA: U1.22 (IO14); also elsewhere on the board
LED5_DATA: U1.8 (IO15); also elsewhere on the board
LED6_DATA: U1.9 (IO16); also elsewhere on the board
LED7_DATA: U1.10 (IO17); also elsewhere on the board
LED8_DATA: U1.11 (IO18); also elsewhere on the board
LED_ISENSE: U1.38 (IO2); also elsewhere on the board
SENS_5V_FLT: U1.24 (IO47); also elsewhere on the board
STATUS_LED: R16.1; also elsewhere on the board
STATUS_LED_A: D9.2 (A), R16.2
UART0_RX: J4.4, U1.36 (RXD0)
UART0_TX: J4.3, U1.37 (TXD0)
USB_CC1: J3.A5 (CC1), R17.1
USB_CC2: J3.B5 (CC2), R18.1
USB_DN: J3.A7 (D-), J3.B7 (D-), U1.13 (USB_D-), U9.1 (I/O1), U9.6 (I/O1)
USB_DP: J3.A6 (D+), J3.B6 (D+), U1.14 (USB_D+), U9.3 (I/O2), U9.4 (I/O2)
VBAT_SENSE: U1.39 (IO1); also elsewhere on the board
VBUS_USB: D8.2 (A), J3.A4 (VBUS), J3.A9 (VBUS), J3.B4 (VBUS), J3.B9 (VBUS), U9.5 (VBUS)
